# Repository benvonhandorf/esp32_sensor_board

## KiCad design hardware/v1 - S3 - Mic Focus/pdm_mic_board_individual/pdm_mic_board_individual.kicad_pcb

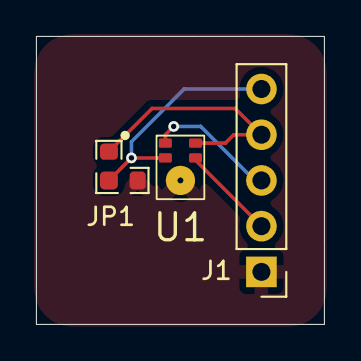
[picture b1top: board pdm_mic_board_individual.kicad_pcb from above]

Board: 2 copper layers, 16.0 x 16.0 mm, 3 parts (0 on the bottom side), 5 nets.

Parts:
J1: Mic Conn; PinHeader_1x05_P2.54mm_Vertical
JP1: L/R; Jumper_Resistor_0603_2_Way
U1: Knowles_PDM_SMD_ThroughPort

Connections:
+3.3V: J1.4, JP1.1 (A), U1.5 (Vcc)
/Dout: J1.3, U1.1 (Dout)
/SCLK: J1.2, U1.4 (CLK)
/SEL: J1.5, JP1.2 (COM), U1.2 (SEL)
GND: J1.1, JP1.3 (B), U1.3 (GND)

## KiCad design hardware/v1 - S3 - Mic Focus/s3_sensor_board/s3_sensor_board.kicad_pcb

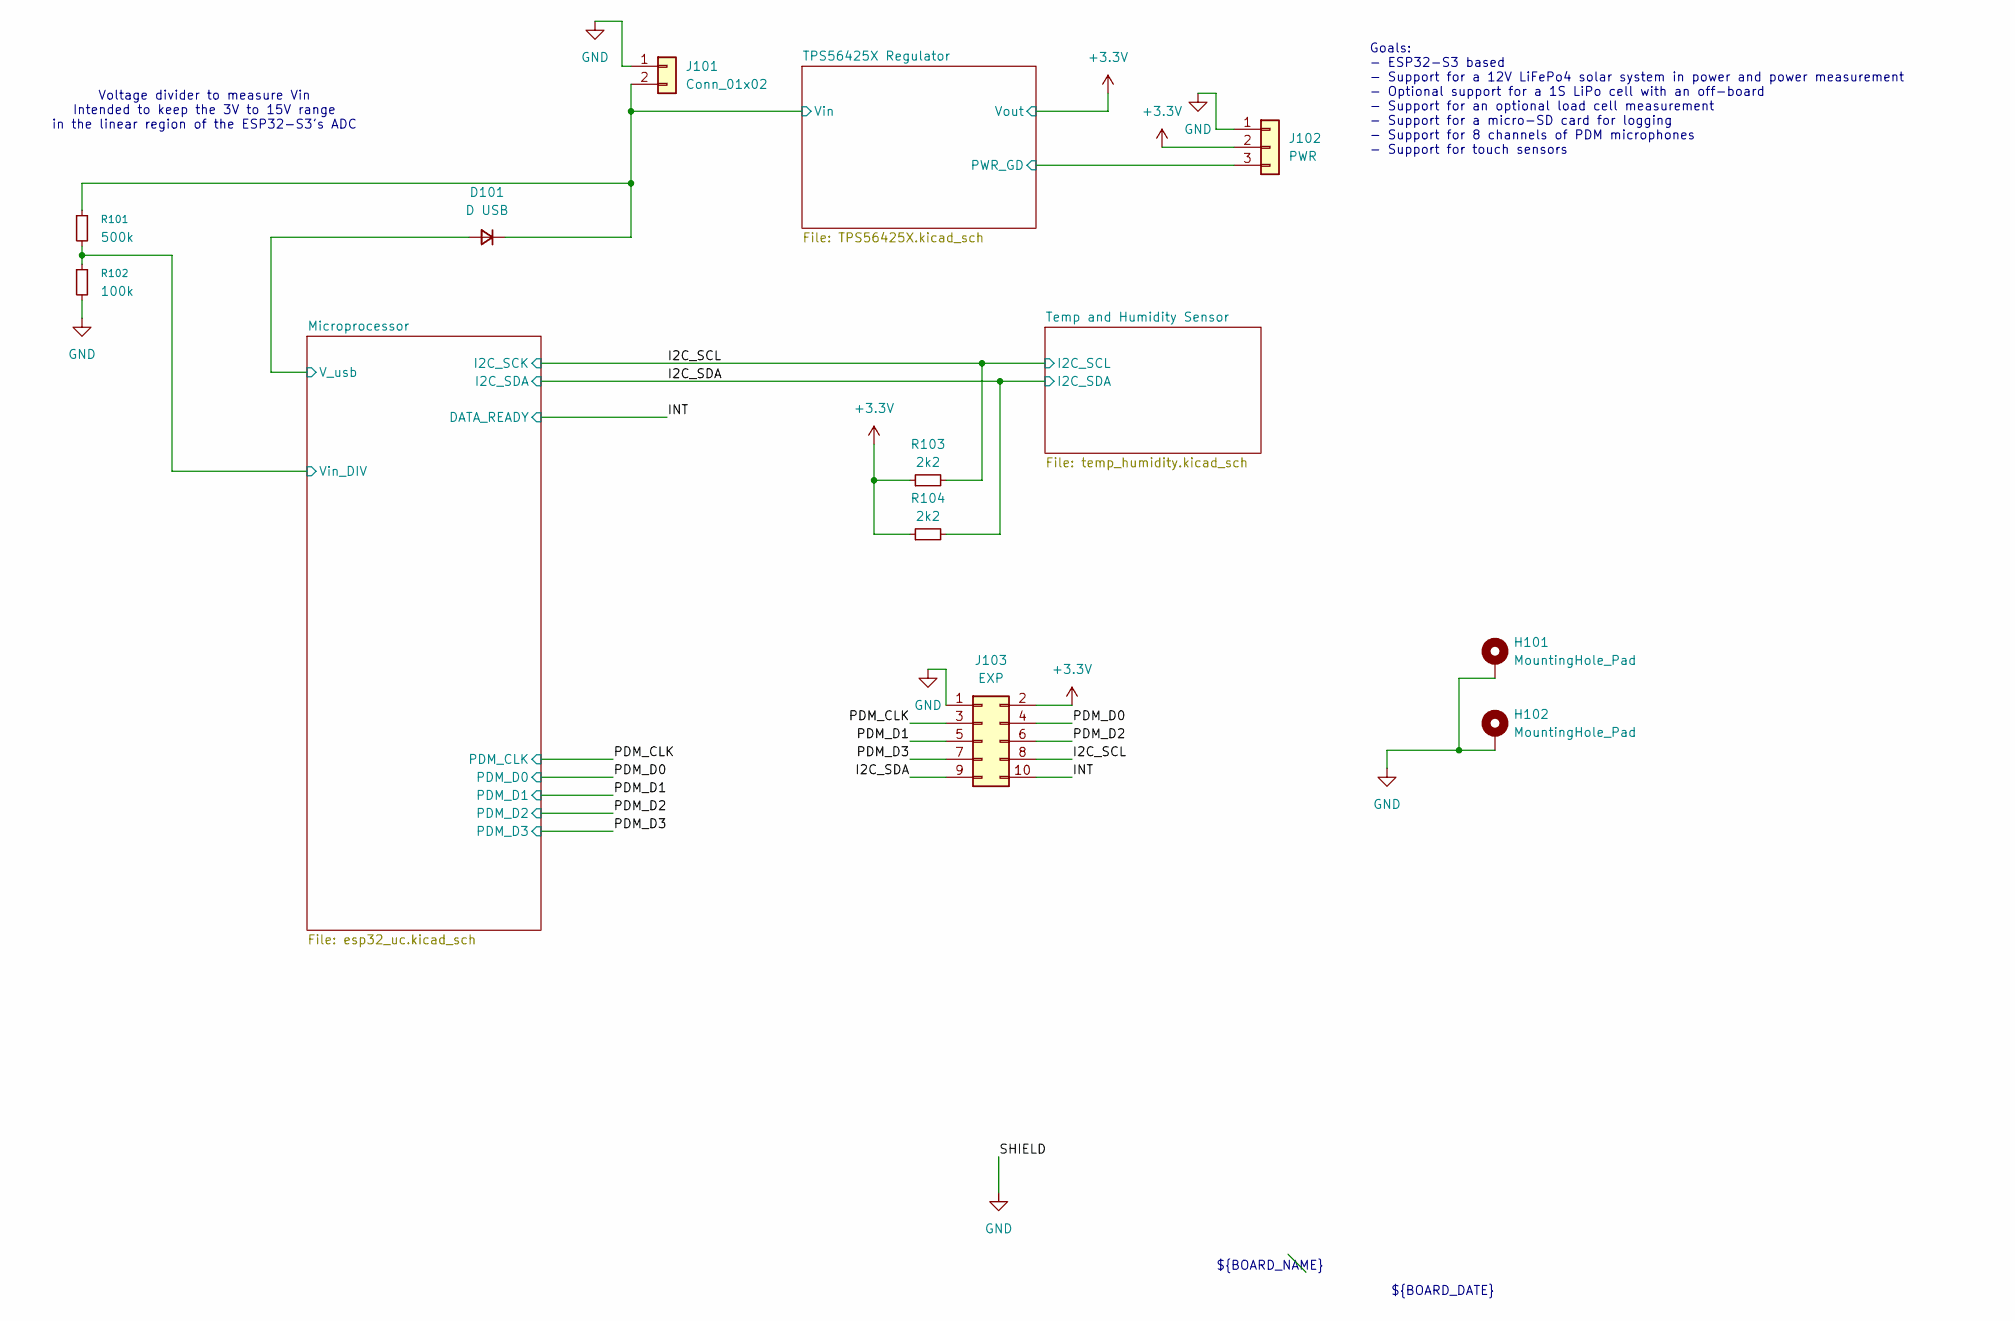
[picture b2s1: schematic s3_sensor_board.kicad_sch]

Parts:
D101: D USB; D_SOD-123
H101, H102: MountingHole_Pad; MountingHole_2.2mm_M2_DIN965_Pad
J101: Conn_01x02; PinHeader_1x02_P2.54mm_Vertical
J102: PWR; PinHeader_1x03_P2.54mm_Vertical
J103: EXP; IDC-Header_2x05_P2.54mm_Vertical
R101: 500k; R_0603_1608Metric
R102: 100k; R_0603_1608Metric
R103, R104: 2k2; R_0603_1608Metric

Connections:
+3.3V: J102.2, J103.2, R103.1, R104.1; also elsewhere on the board
/I2C_SCL: J103.8, R103.2; also elsewhere on the board
/I2C_SDA: J103.9, R104.2; also elsewhere on the board
/INT: J103.10; also elsewhere on the board
/Microprocessor/V_usb: D101.2 (A); also elsewhere on the board
/Microprocessor/Vin_DIV: R101.2, R102.1; also elsewhere on the board
/PDM_CLK: J103.3; also elsewhere on the board
/PDM_D0: J103.4; also elsewhere on the board
/PDM_D1: J103.5; also elsewhere on the board
/PDM_D2: J103.6; also elsewhere on the board
/PDM_D3: J103.7; also elsewhere on the board
/TPS56425X Regulator/PWR_GD: J102.3; also elsewhere on the board
/TPS56425X Regulator/Vin: D101.1 (K), J101.2, R101.1; also elsewhere on the board
GND: H101.1 (1_1), H102.1 (1_1), J101.1, J102.1, J103.1, R102.2; also elsewhere on the board

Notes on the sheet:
${BOARD_DATE}
Goals: - ESP32-S3 based - Support for a 12V LiFePo4 solar system in power and power measurement - Optional support for a 1S LiPo cell with an off-board - Support for an optional load cell measurement - Support for a micro-SD card for logging - Support for 8 channels of PDM microphones - Support for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
${BOARD_NAME}
Voltage divider to measure Vin Intended to keep the 3V to 15V range in the linear region of the ESP32-S3's ADC

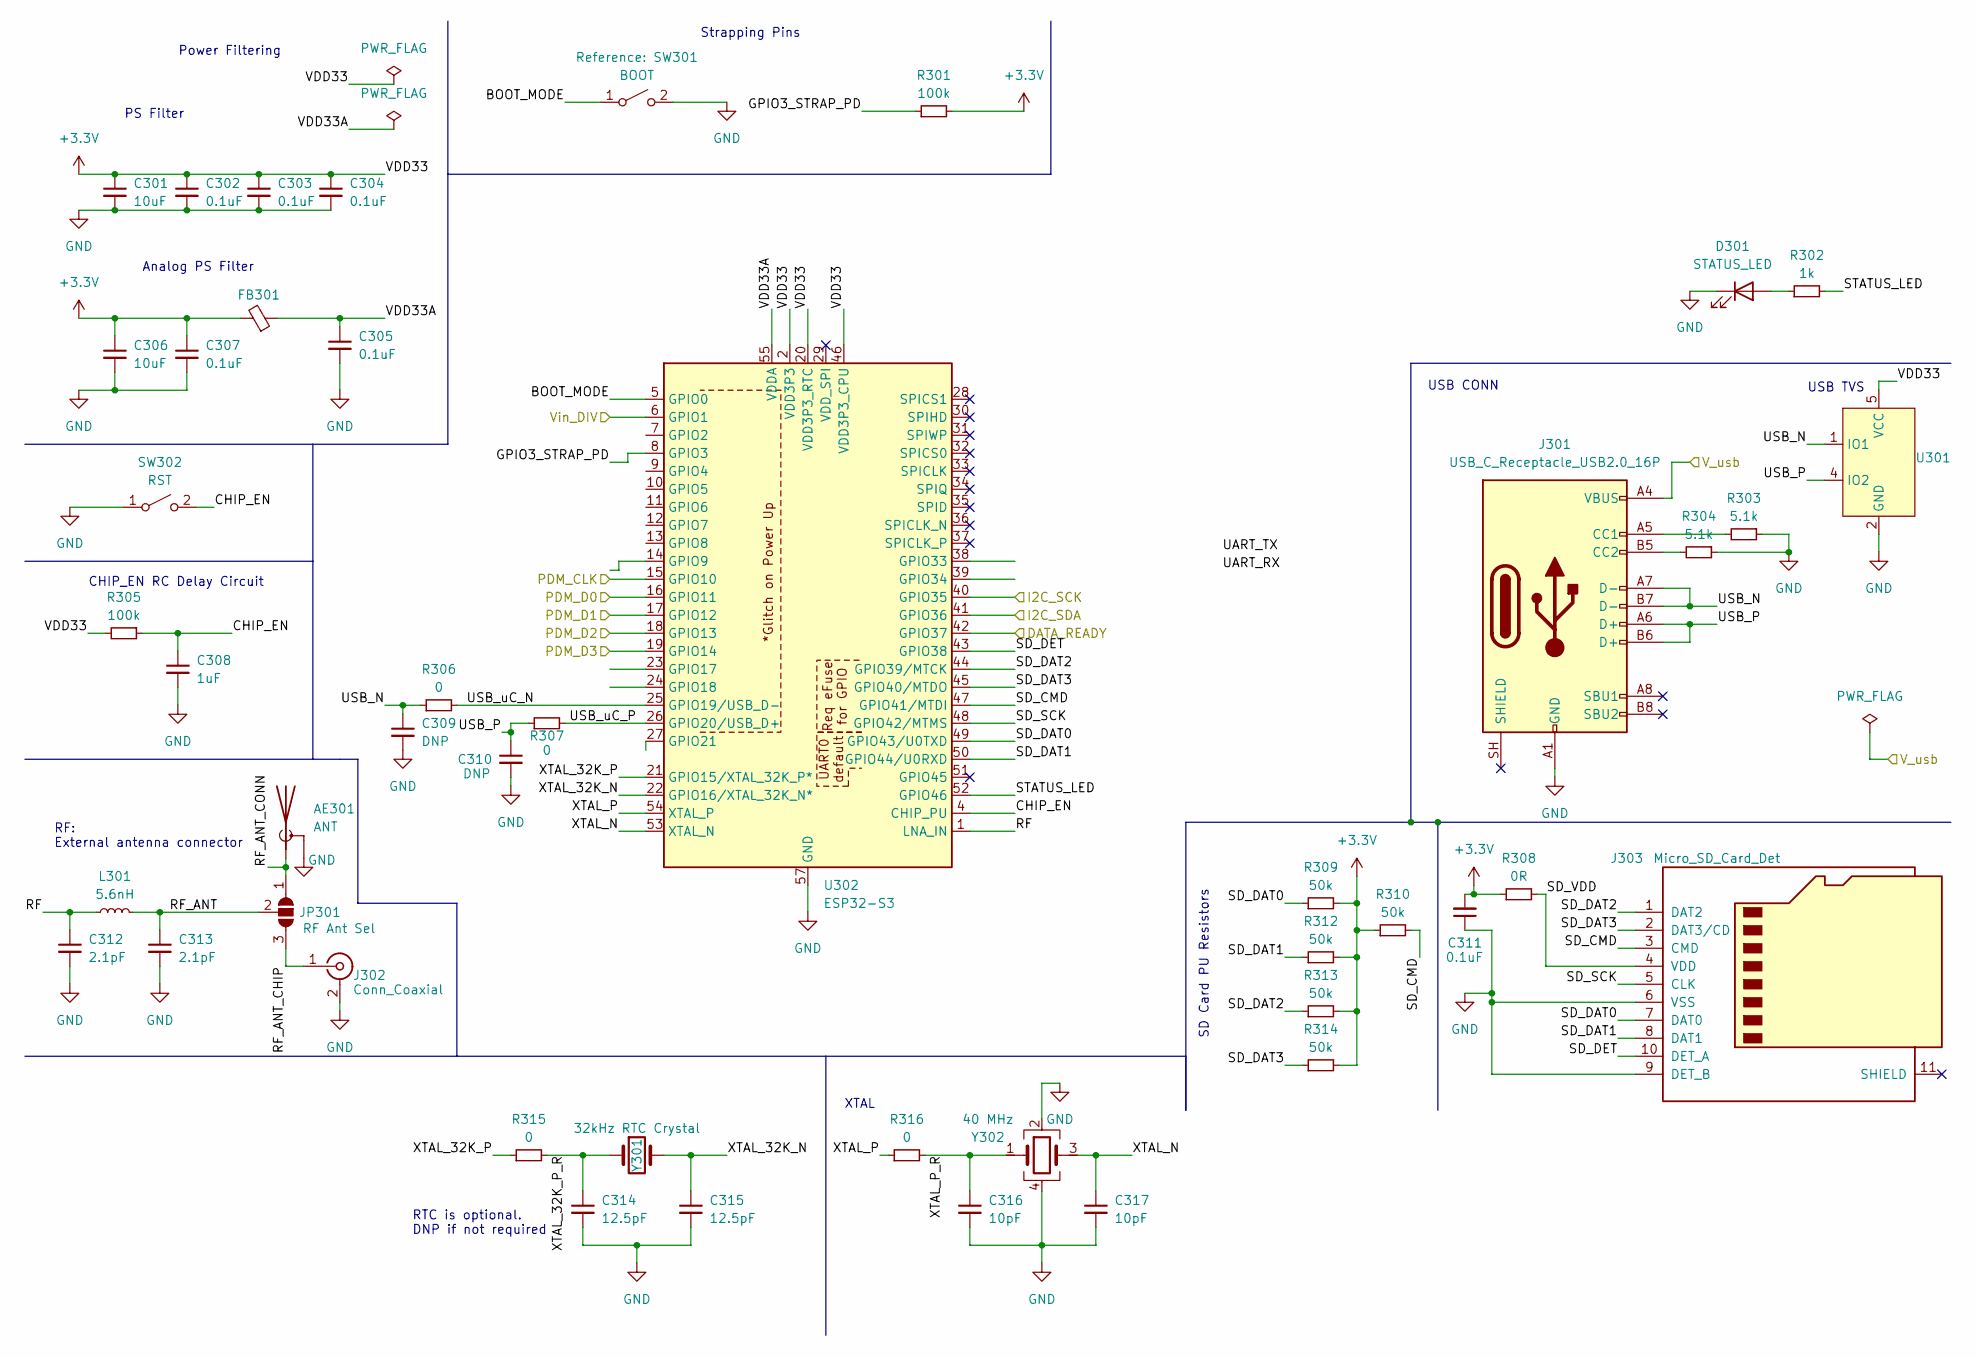
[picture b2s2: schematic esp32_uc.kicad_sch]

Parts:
AE301: ANT; ANT2012LL13R2400A
C301, C306: 10uF; C_0805_2012Metric
C302, C303, C304, C305, C307, C311: 0.1uF; C_0603_1608Metric
C308: 1uF; C_0805_2012Metric
C309, C310: DNP; C_0603_1608Metric
C312, C313: 2.1pF; C_0603_1608Metric
C314, C315: 12.5pF; C_0603_1608Metric
C316, C317: 10pF; C_0603_1608Metric
D301: STATUS_LED; LED_0805_2012Metric
FB301: R_0805_2012Metric
J301: USB_C_Receptacle_USB2.0_16P; USB_C_Receptacle_GCT_USB4085
J302: Conn_Coaxial; U.FL_Molex_MCRF_73412-0110_Vertical
J303: Micro_SD_Card_Det; MicroSD_Socket_Unbranded
JP301: RF Ant Sel; Jumper_Resistor_0603_2_Way
L301: 5.6nH; L_0603_1608Metric
R301, R305: 100k; R_0603_1608Metric
R302: 1k; R_0603_1608Metric
R303, R304: 5.1k; R_0603_1608Metric
R306, R307, R315, R316: 0; R_0603_1608Metric
R308: 0R; R_0603_1608Metric
R309, R310, R312, R313, R314: 50k; R_0603_1608Metric
SW301: BOOT; TacButton_SMD_4.0x3.0mm_SPST_NO_2P
SW302: RST; TacButton_SMD_4.0x3.0mm_SPST_NO_2P
U301: SOT-23-6
U302: ESP32-S3; QFN-56-1EP_7x7mm_P0.4mm_EP4x4mm
Y301: 32kHz RTC Crystal; Crystal_SMD_3215-2Pin_3.2x1.5mm
Y302: 40 MHz; Crystal_SMD_2016-4Pin_2.0x1.6mm

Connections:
+3.3V: C301.1, C302.1, C303.1, C304.1, C306.1, C307.1, C311.2, FB301.2, R301.2, R305.2, R308.1, R309.2, R310.1, R312.2, R313.2, R314.2, U301.5 (VCC), U302.2 (VDD3P3), U302.3 (VDD3P3), U302.20 (VDD3P3_RTC), U302.46 (VDD3P3_CPU); also elsewhere on the board
/I2C_SCL: U302.40 (GPIO35); also elsewhere on the board
/I2C_SDA: U302.41 (GPIO36); also elsewhere on the board
/INT: U302.42 (GPIO37); also elsewhere on the board
/Microprocessor/BOOT_MODE: SW301.1 (A), U302.5 (GPIO0)
/Microprocessor/CHIP_EN: C308.1, R305.1, SW302.2 (B), U302.4 (CHIP_PU)
/Microprocessor/GPIO3_STRAP_PD: R301.1, U302.8 (GPIO3)
/Microprocessor/RF: C312.1, L301.1, U302.1 (LNA_IN)
/Microprocessor/RF_ANT: C313.1, JP301.2 (C), L301.2
/Microprocessor/RF_ANT_CHIP: J302.1 (In), JP301.3 (B)
/Microprocessor/RF_ANT_CONN: AE301.1 (A), JP301.1 (A)
/Microprocessor/SD_CMD: J303.3 (CMD), R310.2, U302.47 (GPIO41/MTDI)
/Microprocessor/SD_DAT0: J303.7 (DAT0), R309.1, U302.49 (GPIO43/U0TXD)
/Microprocessor/SD_DAT1: J303.8 (DAT1), R312.1, U302.50 (GPIO44/U0RXD)
/Microprocessor/SD_DAT2: J303.1 (DAT2), R313.1, U302.44 (GPIO39/MTCK)
/Microprocessor/SD_DAT3: J303.2 (DAT3/CD), R314.1, U302.45 (GPIO40/MTDO)
/Microprocessor/SD_DET: J303.10 (DET_A), U302.43 (GPIO38)
/Microprocessor/SD_SCK: J303.5 (CLK), U302.48 (GPIO42/MTMS)
/Microprocessor/SD_VDD: J303.4 (VDD), R308.2
/Microprocessor/STATUS_LED: R302.2, U302.52 (GPIO46)
/Microprocessor/USB_N: C309.1, J301.A7 (D-), J301.B7 (D-), R306.1, U301.1 (IO1)
/Microprocessor/USB_P: C310.1, J301.A6 (D+), J301.B6 (D+), R307.1, U301.4 (IO2)
/Microprocessor/USB_uC_N: R306.2, U302.25 (GPIO19/USB_D-)
/Microprocessor/USB_uC_P: R307.2, U302.26 (GPIO20/USB_D+)
/Microprocessor/VDD33A: C305.1, FB301.1, U302.55 (VDDA), U302.56 (VDDA)
/Microprocessor/V_usb: J301.A4 (VBUS), J301.A9 (VBUS), J301.B4 (VBUS), J301.B9 (VBUS); also elsewhere on the board
/Microprocessor/Vin_DIV: U302.6 (GPIO1); also elsewhere on the board
/Microprocessor/XTAL_32K_N: C315.1, U302.22 (GPIO16/XTAL_32K_N*), Y301.2
/Microprocessor/XTAL_32K_P: R315.1, U302.21 (GPIO15/XTAL_32K_P*)
/Microprocessor/XTAL_32K_P_R: C314.1, R315.2, Y301.1
/Microprocessor/XTAL_N: C317.1, U302.53 (XTAL_N), Y302.3
/Microprocessor/XTAL_P: R316.1, U302.54 (XTAL_P)
/Microprocessor/XTAL_P_R: C316.1, R316.2, Y302.1
/PDM_CLK: U302.15 (GPIO10); also elsewhere on the board
/PDM_D0: U302.16 (GPIO11); also elsewhere on the board
/PDM_D1: U302.17 (GPIO12); also elsewhere on the board
/PDM_D2: U302.18 (GPIO13); also elsewhere on the board
/PDM_D3: U302.19 (GPIO14); also elsewhere on the board
GND: AE301.2 (GND), C301.2, C302.2, C303.2, C304.2, C305.2, C306.2, C307.2, C308.2, C309.2, C310.2, C311.1, C312.2, C313.2, C314.2, C315.2, C316.2, C317.2, D301.1 (K), J301.A1 (GND), J301.A12 (GND), J301.B1 (GND), J301.B12 (GND), J302.2 (Ext), J303.6 (VSS), J303.9 (DET_B), R303.1, R304.1, SW301.2 (B), SW302.1 (A), U301.2 (GND), U302.57 (GND), Y302.2, Y302.4; also elsewhere on the board
unnamed: D301.2 (A), R302.1
unnamed: J301.A5 (CC1), R303.2
unnamed: J301.B5 (CC2), R304.2

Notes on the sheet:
CHIP_EN RC Delay Circuit
Analog PS Filter
SD Card PU Resistors
XTAL
USB CONN
RTC is optional. DNP if not required
USB TVS
Strapping Pins
Power Filtering
PS Filter
RF: External antenna connector

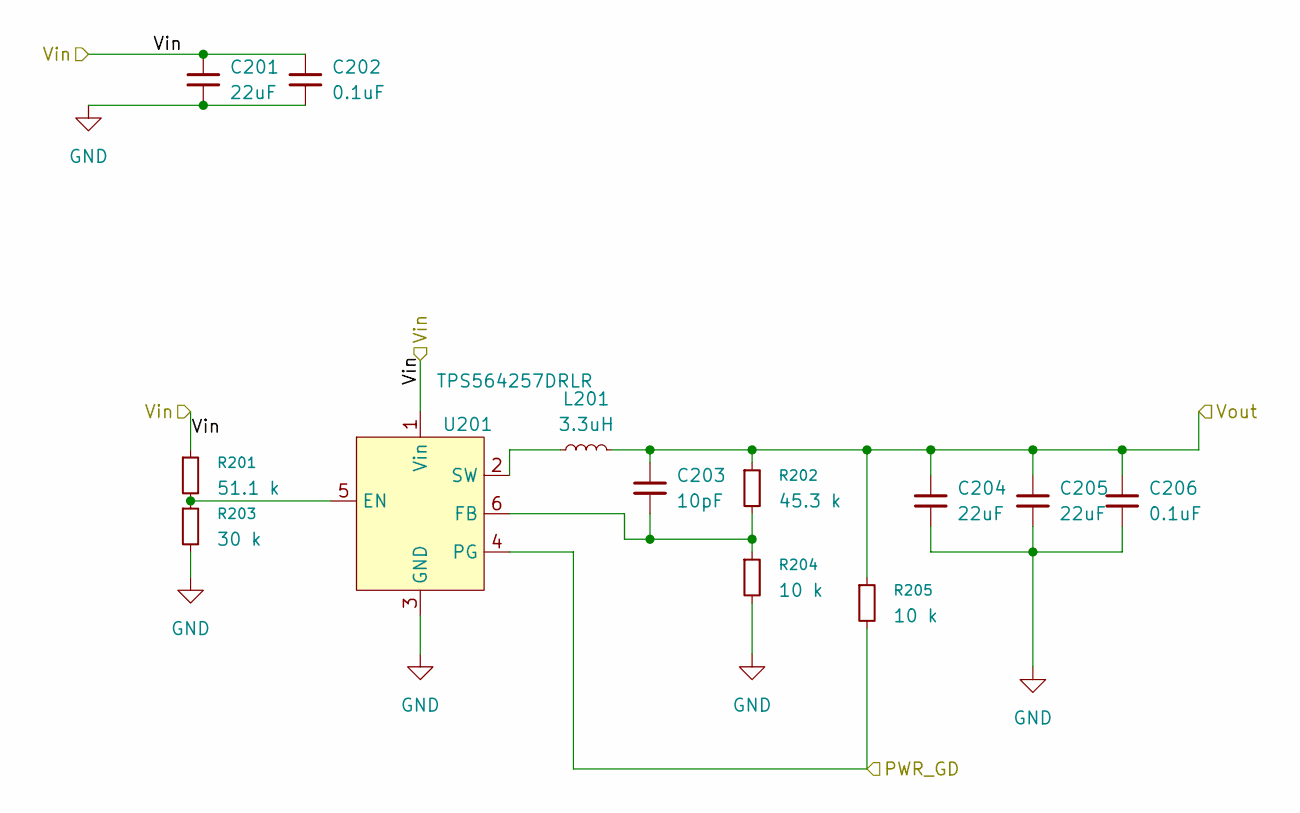
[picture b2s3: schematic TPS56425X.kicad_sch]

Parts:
C201, C204, C205: 22uF; C_0805_2012Metric; MPN GRM21BR61E226ME44L
C202, C206: 0.1uF; C_0603_1608Metric
C203: 10pF; C_0805_2012Metric
L201: 3.3uH; L_Taiyo-Yuden_MD-2020
R201: 51.1 k; R_0603_1608Metric
R202: 45.3 k; R_0603_1608Metric; MPN RC0603FR-0745K3L
R203: 30 k; R_0603_1608Metric
R204, R205: 10 k; R_0603_1608Metric
U201: TPS564257DRLR; SOT-563

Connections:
+3.3V: C203.1, C204.1, C205.1, C206.1, L201.2, R202.1, R205.1; also elsewhere on the board
/TPS56425X Regulator/PWR_GD: R205.2, U201.4 (PG); also elsewhere on the board
/TPS56425X Regulator/Vin: C201.1, C202.1, R201.1, U201.1 (Vin); also elsewhere on the board
GND: C201.2, C202.2, C204.2, C205.2, C206.2, R203.2, R204.2, U201.3 (GND); also elsewhere on the board
unnamed: R201.2, R203.1, U201.5 (EN)
unnamed: C203.2, R202.2, R204.1, U201.6 (FB)
unnamed: L201.1, U201.2 (SW)

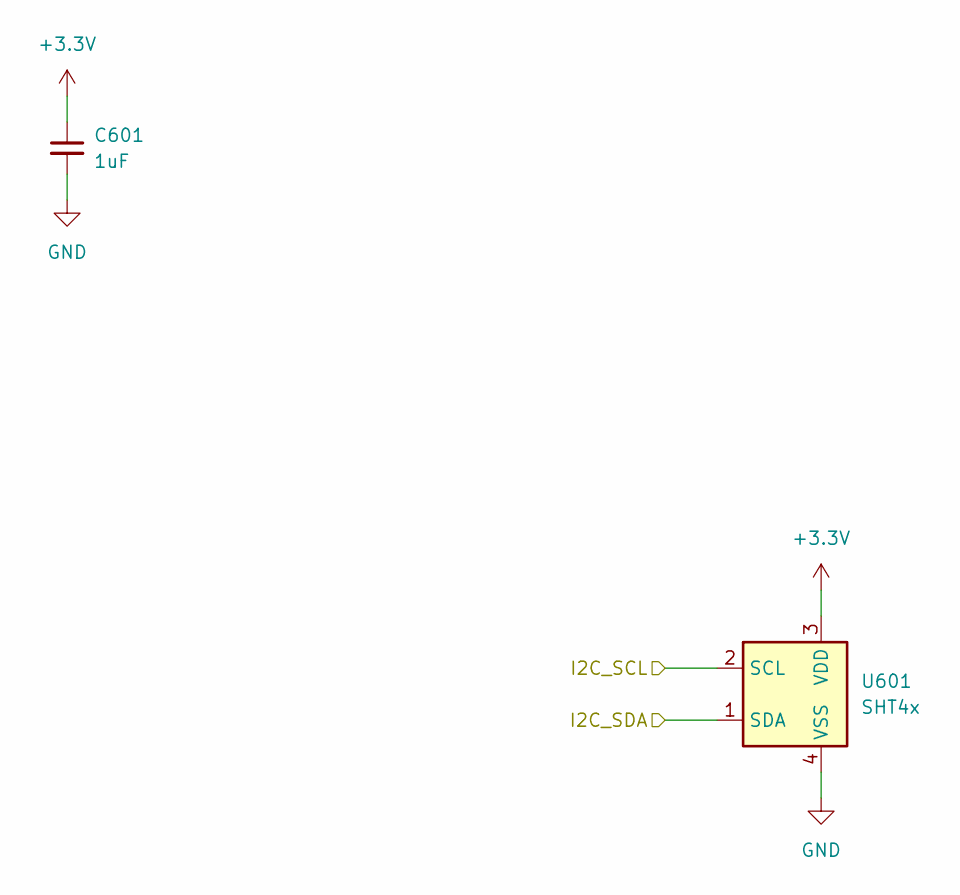
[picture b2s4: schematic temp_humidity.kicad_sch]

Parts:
C601: 1uF; C_0805_2012Metric
U601: SHT4x; Sensirion_DFN-4_1.5x1.5mm_P0.8mm_SHT4x_NoCentralPad

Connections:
unnamed: C601.1, U601.3 (VDD)
unnamed: C601.2, U601.4 (VSS)

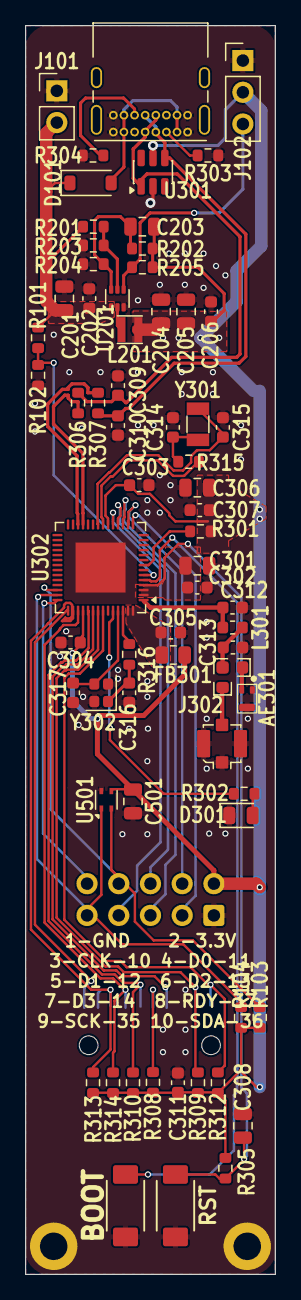
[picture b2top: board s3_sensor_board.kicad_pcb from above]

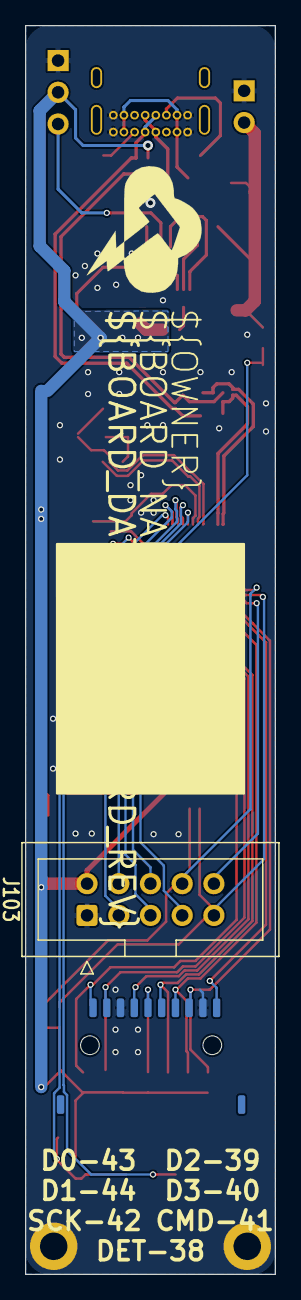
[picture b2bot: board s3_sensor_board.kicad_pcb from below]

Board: 4 copper layers, 20.0 x 100.0 mm, 71 parts (2 on the bottom side), 47 nets.

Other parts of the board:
C501: 1uF; C_0805_2012Metric
U501: SHT4x; Sensirion_DFN-4_1.5x1.5mm_P0.8mm_SHT4x_NoCentralPad

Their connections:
+3.3V: C501.1, U501.3 (VDD); also elsewhere on the board
/I2C_SCL: U501.2 (SCL); also elsewhere on the board
/I2C_SDA: U501.1 (SDA); also elsewhere on the board
GND: C501.2, U501.4 (VSS); also elsewhere on the board

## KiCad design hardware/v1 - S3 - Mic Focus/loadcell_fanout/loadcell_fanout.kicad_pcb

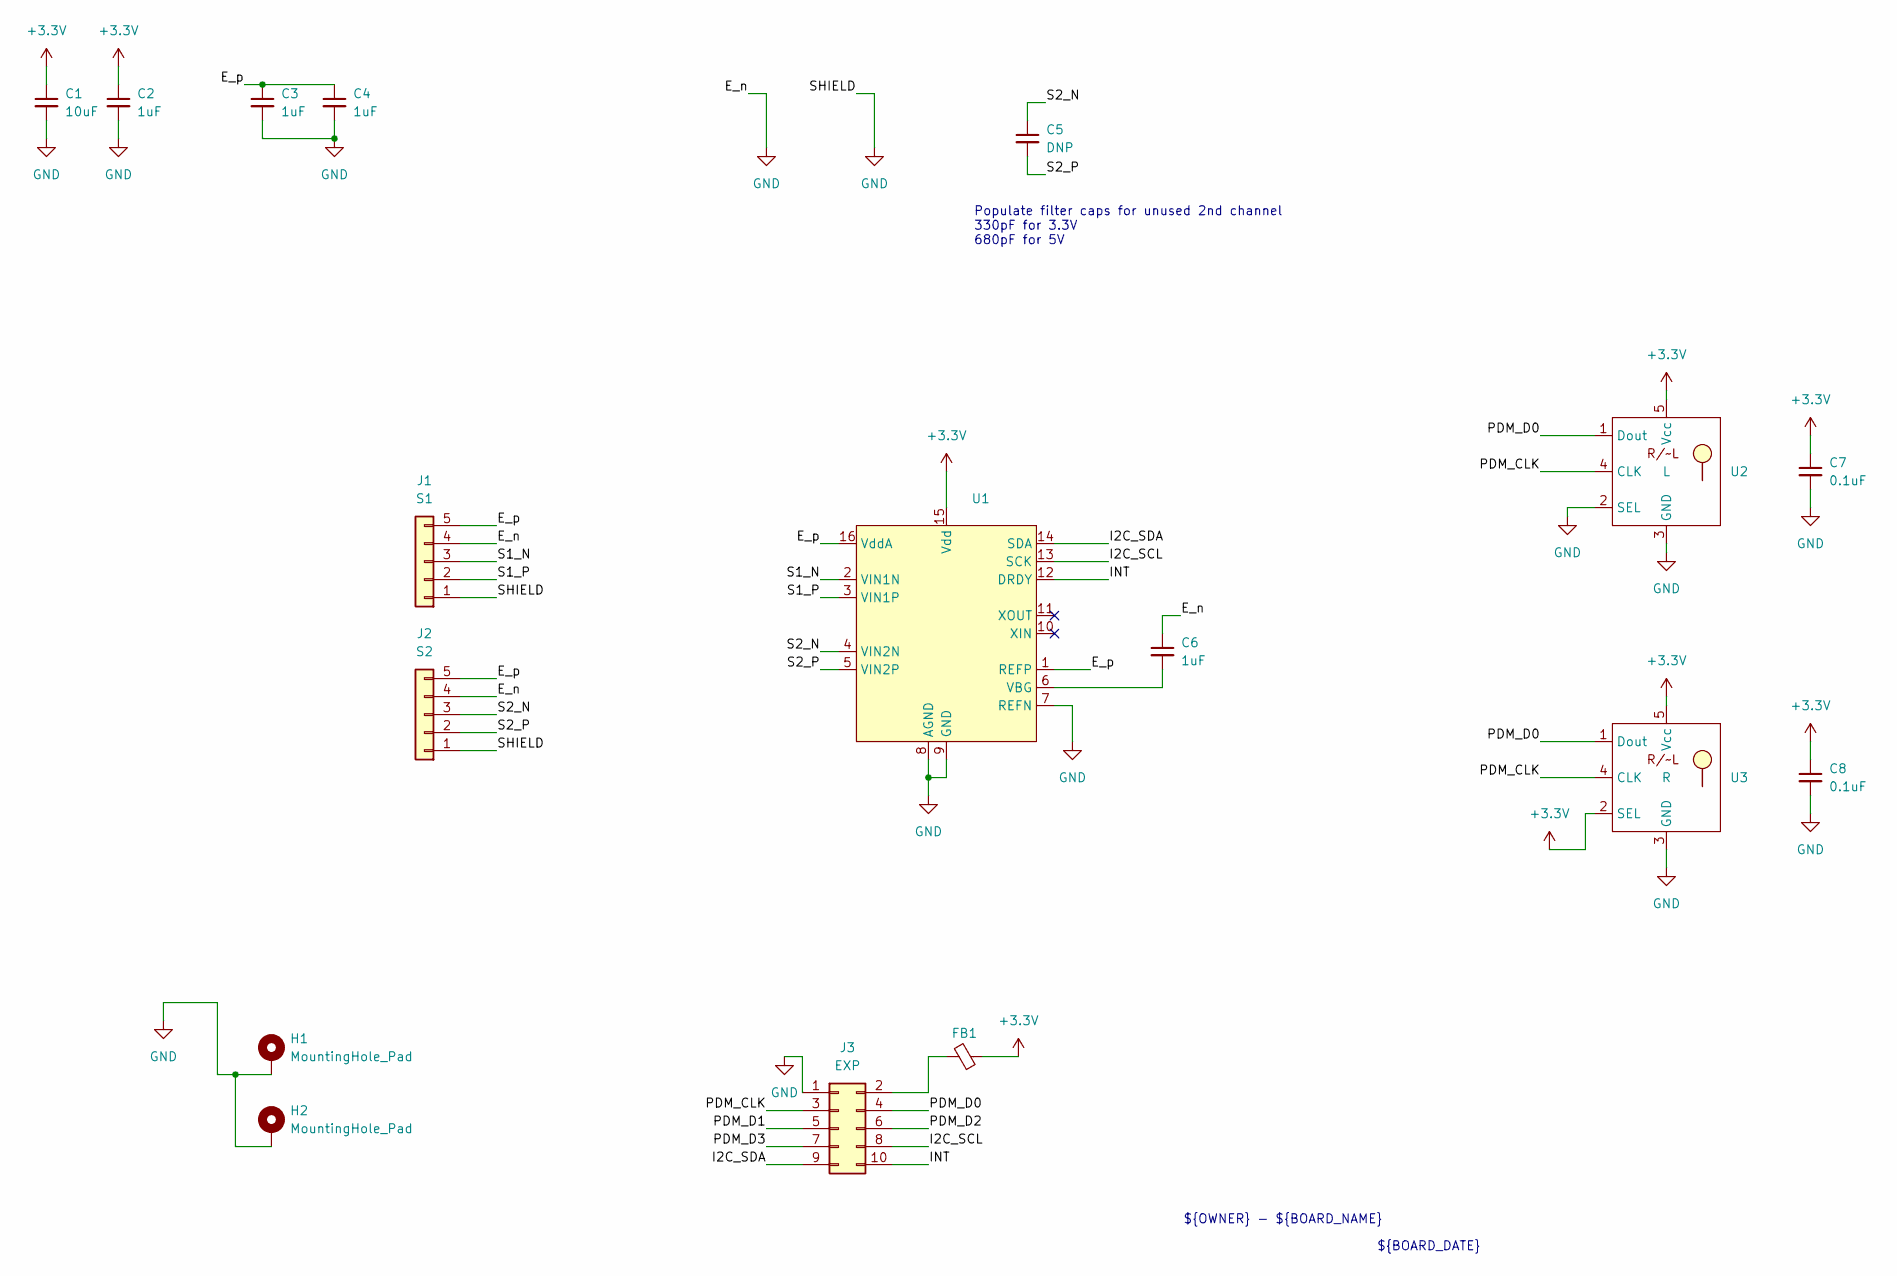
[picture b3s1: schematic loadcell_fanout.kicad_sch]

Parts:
C1: 10uF; C_0805_2012Metric
C2, C3, C4, C6: 1uF; C_0805_2012Metric
C5: DNP; C_0805_2012Metric
C7, C8: 0.1uF; C_0603_1608Metric
FB1: R_0805_2012Metric
H1, H2: MountingHole_Pad; MountingHole_2.2mm_M2_DIN965_Pad
J1: S1; PinHeader_1x05_P2.54mm_Vertical
J2: S2; PinHeader_1x05_P2.54mm_Vertical
J3: EXP; Conn_IDC_Female_Board_Mount_02x05_Abomination
U1: SOIC-16_3.9x9.9mm_P1.27mm
U2: L; Knowles_PDM_SMD_ThroughPort
U3: R; Knowles_PDM_SMD_ThroughPort

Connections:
+3.3V: C1.1, C2.1, C7.1, C8.1, FB1.1, U1.15 (Vdd), U2.5 (Vcc), U3.2 (SEL), U3.5 (Vcc)
/E_p: C3.1, C4.1, J1.5, J2.5, U1.1 (REFP), U1.16 (VddA)
/I2C_SCL: J3.8, U1.13 (SCK)
/I2C_SDA: J3.9, U1.14 (SDA)
/INT: J3.10, U1.12 (DRDY)
/PDM_CLK: J3.3, U2.4 (CLK), U3.4 (CLK)
/PDM_D0: J3.4, U2.1 (Dout), U3.1 (Dout)
/PDM_D1: J3.5
/PDM_D2: J3.6
/PDM_D3: J3.7
/S1_N: J1.3, U1.2 (VIN1N)
/S1_P: J1.2, U1.3 (VIN1P)
/S2_N: C5.1, J2.3, U1.4 (VIN2N)
/S2_P: C5.2, J2.2, U1.5 (VIN2P)
GND: C1.2, C2.2, C3.2, C4.2, C6.1, C7.2, C8.2, H1.1 (1_1), H2.1 (1_1), J1.1, J1.4, J2.1, J2.4, J3.1, U1.7 (REFN), U1.8 (AGND), U1.9 (GND), U2.2 (SEL), U2.3 (GND), U3.3 (GND)
unnamed: FB1.2, J3.2
unnamed: C6.2, U1.6 (VBG)

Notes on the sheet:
Populate filter caps for unused 2nd channel 330pF for 3.3V 680pF for 5V
${OWNER} - ${BOARD_NAME}
${BOARD_DATE}

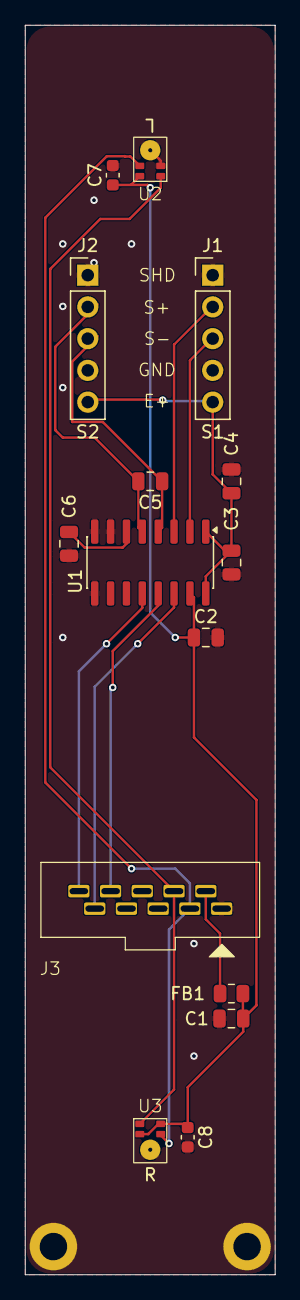
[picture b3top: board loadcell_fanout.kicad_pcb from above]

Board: 4 copper layers, 20.0 x 100.0 mm, 17 parts (0 on the bottom side), 14 nets.

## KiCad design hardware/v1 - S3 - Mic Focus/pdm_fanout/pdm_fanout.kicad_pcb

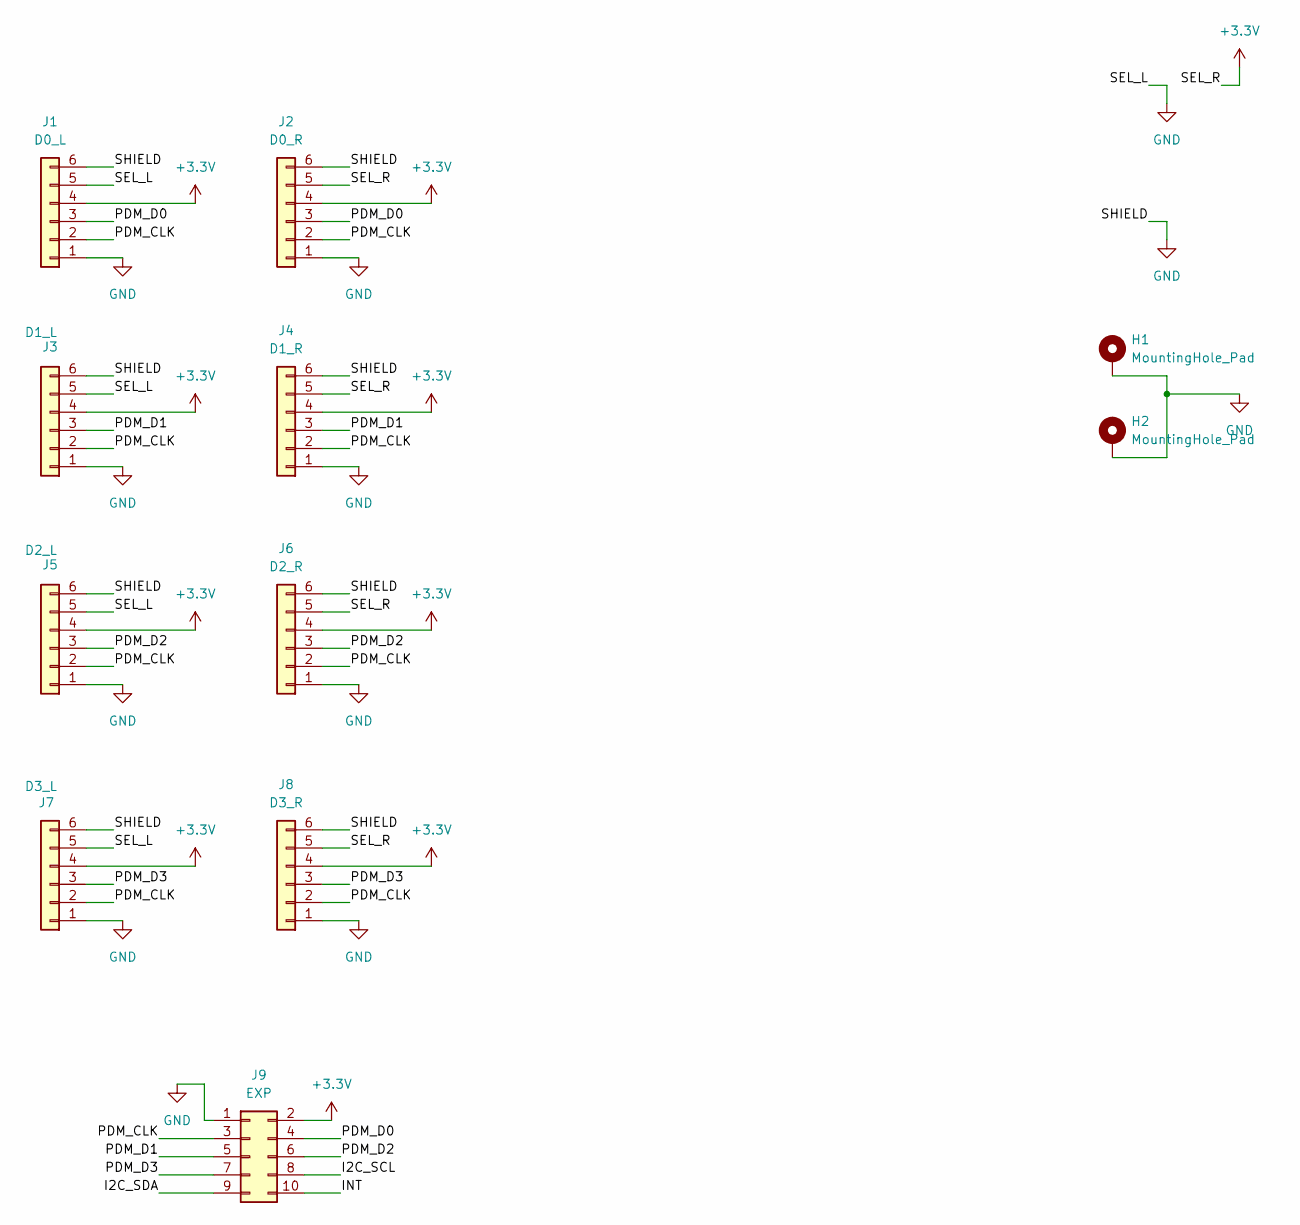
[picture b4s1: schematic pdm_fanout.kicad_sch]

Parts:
H1, H2: MountingHole_Pad; MountingHole_2.2mm_M2_DIN965_Pad
J1: D0_L; PinHeader_1x06_P2.54mm_Vertical
J2: D0_R; PinHeader_1x06_P2.54mm_Vertical
J3: D1_L; PinHeader_1x06_P2.54mm_Vertical
J4: D1_R; PinHeader_1x06_P2.54mm_Vertical
J5: D2_L; PinHeader_1x06_P2.54mm_Vertical
J6: D2_R; PinHeader_1x06_P2.54mm_Vertical
J7: D3_L; PinHeader_1x06_P2.54mm_Vertical
J8: D3_R; PinHeader_1x06_P2.54mm_Vertical
J9: EXP; Conn_IDC_Female_Board_Mount_02x05_Abomination

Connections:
+3.3V: J1.4, J2.4, J2.5, J3.4, J4.4, J4.5, J5.4, J6.4, J6.5, J7.4, J8.4, J8.5, J9.2
/I2C_SCL: J9.8
/I2C_SDA: J9.9
/INT: J9.10
/PDM_CLK: J1.2, J2.2, J3.2, J4.2, J5.2, J6.2, J7.2, J8.2, J9.3
/PDM_D0: J1.3, J2.3, J9.4
/PDM_D1: J3.3, J4.3, J9.5
/PDM_D2: J5.3, J6.3, J9.6
/PDM_D3: J7.3, J8.3, J9.7
GND: H1.1 (1_1), H2.1 (1_1), J1.1, J1.5, J1.6, J2.1, J2.6, J3.1, J3.5, J3.6, J4.1, J4.6, J5.1, J5.5, J5.6, J6.1, J6.6, J7.1, J7.5, J7.6, J8.1, J8.6, J9.1

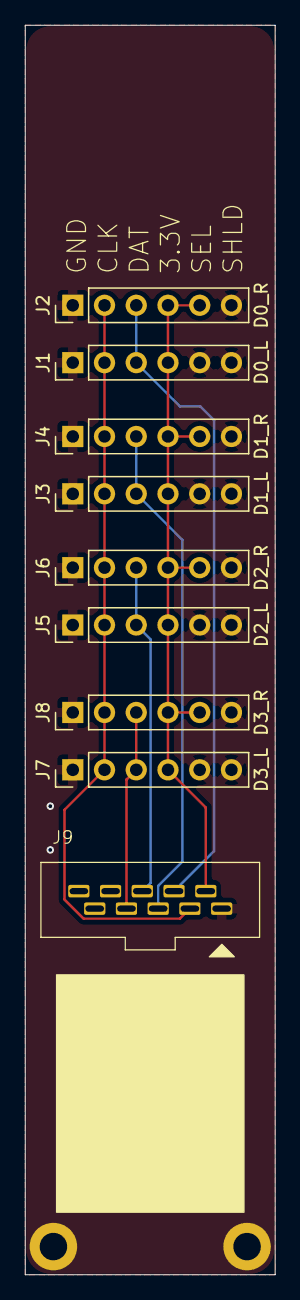
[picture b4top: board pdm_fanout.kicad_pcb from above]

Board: 2 copper layers, 20.0 x 100.0 mm, 11 parts (0 on the bottom side), 7 nets.

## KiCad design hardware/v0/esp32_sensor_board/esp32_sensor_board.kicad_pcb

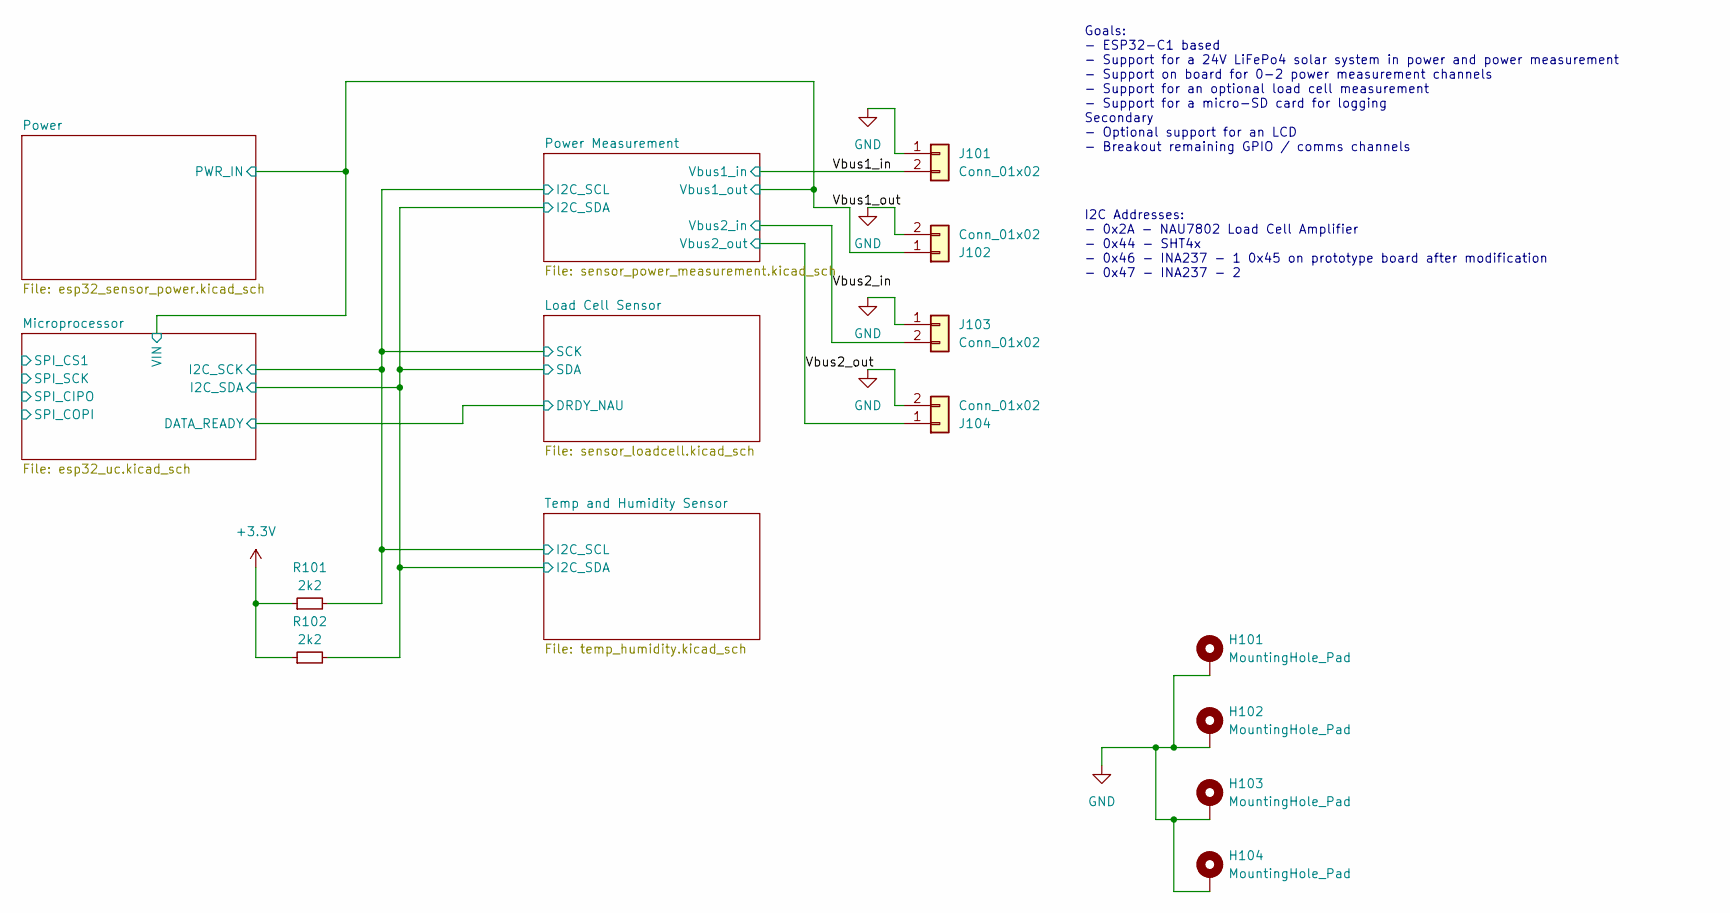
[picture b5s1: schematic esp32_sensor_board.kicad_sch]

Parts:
H101, H102, H103, H104: MountingHole_Pad; MountingHole_3.2mm_M3_DIN965_Pad
J101, J102, J103, J104: Conn_01x02; PhoenixContact_MSTBA_2,5_2-G-5,08_1x02_P5.08mm_Horizontal
R101, R102: 2k2; R_0603_1608Metric

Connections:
+3.3V: R101.1, R102.1; also elsewhere on the board
/Power Measurement/I2C_SCL: R101.2; also elsewhere on the board
/Power Measurement/I2C_SDA: R102.2; also elsewhere on the board
/Vbus1_in: J101.2; also elsewhere on the board
/Vbus2_in: J103.2; also elsewhere on the board
/Vbus2_out: J104.1; also elsewhere on the board
GND: H101.1, H102.1, H103.1, H104.1, J101.1, J102.2, J103.1, J104.2; also elsewhere on the board
VIN: J102.1; also elsewhere on the board

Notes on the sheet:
Goals: - ESP32-C1 based - Support for a 24V LiFePo4 solar system in power and power measurement - Support on board for 0-2 power measurement channels - Support for an optional load cell measurement - Support for a micro-SD card for logging Secondary - Optional support for an LCD - Breakout remainin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
I2C Addresses: - 0x2A - NAU7802 Load Cell Amplifier - 0x44 - SHT4x - 0x46 - INA237 - 1 0x45 on prototype board after modification - 0x47 - INA237 - 2
